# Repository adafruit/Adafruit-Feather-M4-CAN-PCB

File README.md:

## Adafruit Feather M4 CAN Express PCB

<a href="http://www.adafruit.com/products/4759"><br/>
Click here to purchase one from the Adafruit shop</a>

PCB files for the Adafruit Feather M4 CAN Express.

Format is EagleCAD schematic and board layout
* https://www.adafruit.com/product/4759

### Description

One of our favorite Feathers, the Feather M4 Express, gets a glow-up here with an upgrade to the SAME51 chipset which has built-in CAN bus support!  Like its SAMD51 cousin, the ATSAME51J19 comes with a 120MHz Cortex M4 with floating point support and 512KB Flash and 192KB RAM. Your code will zig and zag and zoom, and with a bunch of extra peripherals for support, this will for sure be your favorite new chipset for CAN interfacing projects.

At the end of the board we have placed a CAN transceiver chip as well as a 5V converter to generate 5V power to the transceiver even when running on battery. The two CAN signal lines and ground reference signal are available on a 3-pin 3.5mm terminal block. The chip and booster can be put to sleep for power saving. The built in CAN can read or write packets and has support in both Arduino and CircuitPython.

And best of all, it's a Feather - so you know it will work with all our FeatherWings! What a great way to quickly get up and running. It's even pin-compatible with the original Feather M4.

The most exciting part of the Feather M4 CAN is that while you can use it with the Arduino IDE - and it's bonkers fast when you do, you can use it with CircuitPython as well. When you plug it in, it will show up as a very small disk drive with main.py on it. Edit main.py with your favorite text editor to build your project using Python, the most popular programming language. No installs, IDE or compiler needed, so you can use it on any computer, even ChromeBooks or computers you can't install software on. When you're done, unplug the Feather and your code will go with you.

Here are some of the updates you can look forward to when using Feather M4 CAN:

* Measures 2.0" x 0.9" x 0.28" (50.8mm x 22.8mm x 7mm) without headers soldered in
* Light as a (large?) feather - 5 grams
* ATSAME51 32-bit Cortex M4 core running at 120 MHz, 32-bit, 3.3V logic and power
* Hardware CAN bus support with built-in transceiver, 5V booster and terminal connection.
* Floating point support with Cortex M4 DSP instructions
* 512 KB flash, 192 KB RAM
* 2 MB SPI FLASH chip for storing files and CircuitPython code storage.
* No EEPROM
* 32.768 KHz crystal for clock generation & RTC
* 3.3V regulator with 500mA peak current output
* USB Type C connector for USB native support, comes with USB bootloader and serial port debugging
* Built in crypto engines with AES (256 bit), true RNG, Pubkey controller
* Tons of GPIO! 21 x GPIO pins with following capabilities:
  * Dual 1 MSPS 12 bit true analog DAC (A0 and A1) - can be used to play 12-bit stereo audio clips
  * Dual 1 MSPS 12 bit ADC (6 analog pins some on ADC1 and some on ADC2)
  * 6 x hardware SERCOM - Native hardware SPI, I2C and Serial all available
  * 16 x PWM outputs - for servos, LEDs, etc
  * I2S input and output
  * 8-bit Parallel capture controller (for camera/video in)
* Built in 100mA lipoly charger with charging status indicator LED
* Pin #13 red LED for general purpose blinking
* Power/enable pin
* 4 mounting holes
* Reset button

The Feather M4 Can Express also comes with a Mini NeoPixel and 2 MB SPI Flash storage. You can use the SPI Flash storage like a very tiny hard drive. When used in CircuitPython, the 2 MB flash acts as storage for all your scripts, libraries and files. When used in Arduino, you can read/write files to it, like a little datalogger or SD card, and then with our helper program, access the files over USB.

Easy reprogramming: the Feather M4 CAN comes pre-loaded with the UF2 bootloader, which looks like a USB storage key. Simply drag firmware on to program, no special tools or drivers needed! It can be used to load up CircuitPython or Arduino IDE (it is bossa-compatible)

Comes fully assembled and tested, with the UF2 USB bootloader. We also toss in some headers so you can solder it in and plug into a solderless breadboard.

Lipoly battery and USB cable not included (but we do have lots of options in the shop if you'd like!)

### License

Adafruit invests time and resources providing this open source design, please support Adafruit and open-source hardware by purchasing products from [Adafruit](https://www.adafruit.com)!

Designed by Limor Fried/Ladyada for Adafruit Industries.

Creative Commons Attribution/Share-Alike, all text above must be included in any redistribution.
See license.txt for additional details.

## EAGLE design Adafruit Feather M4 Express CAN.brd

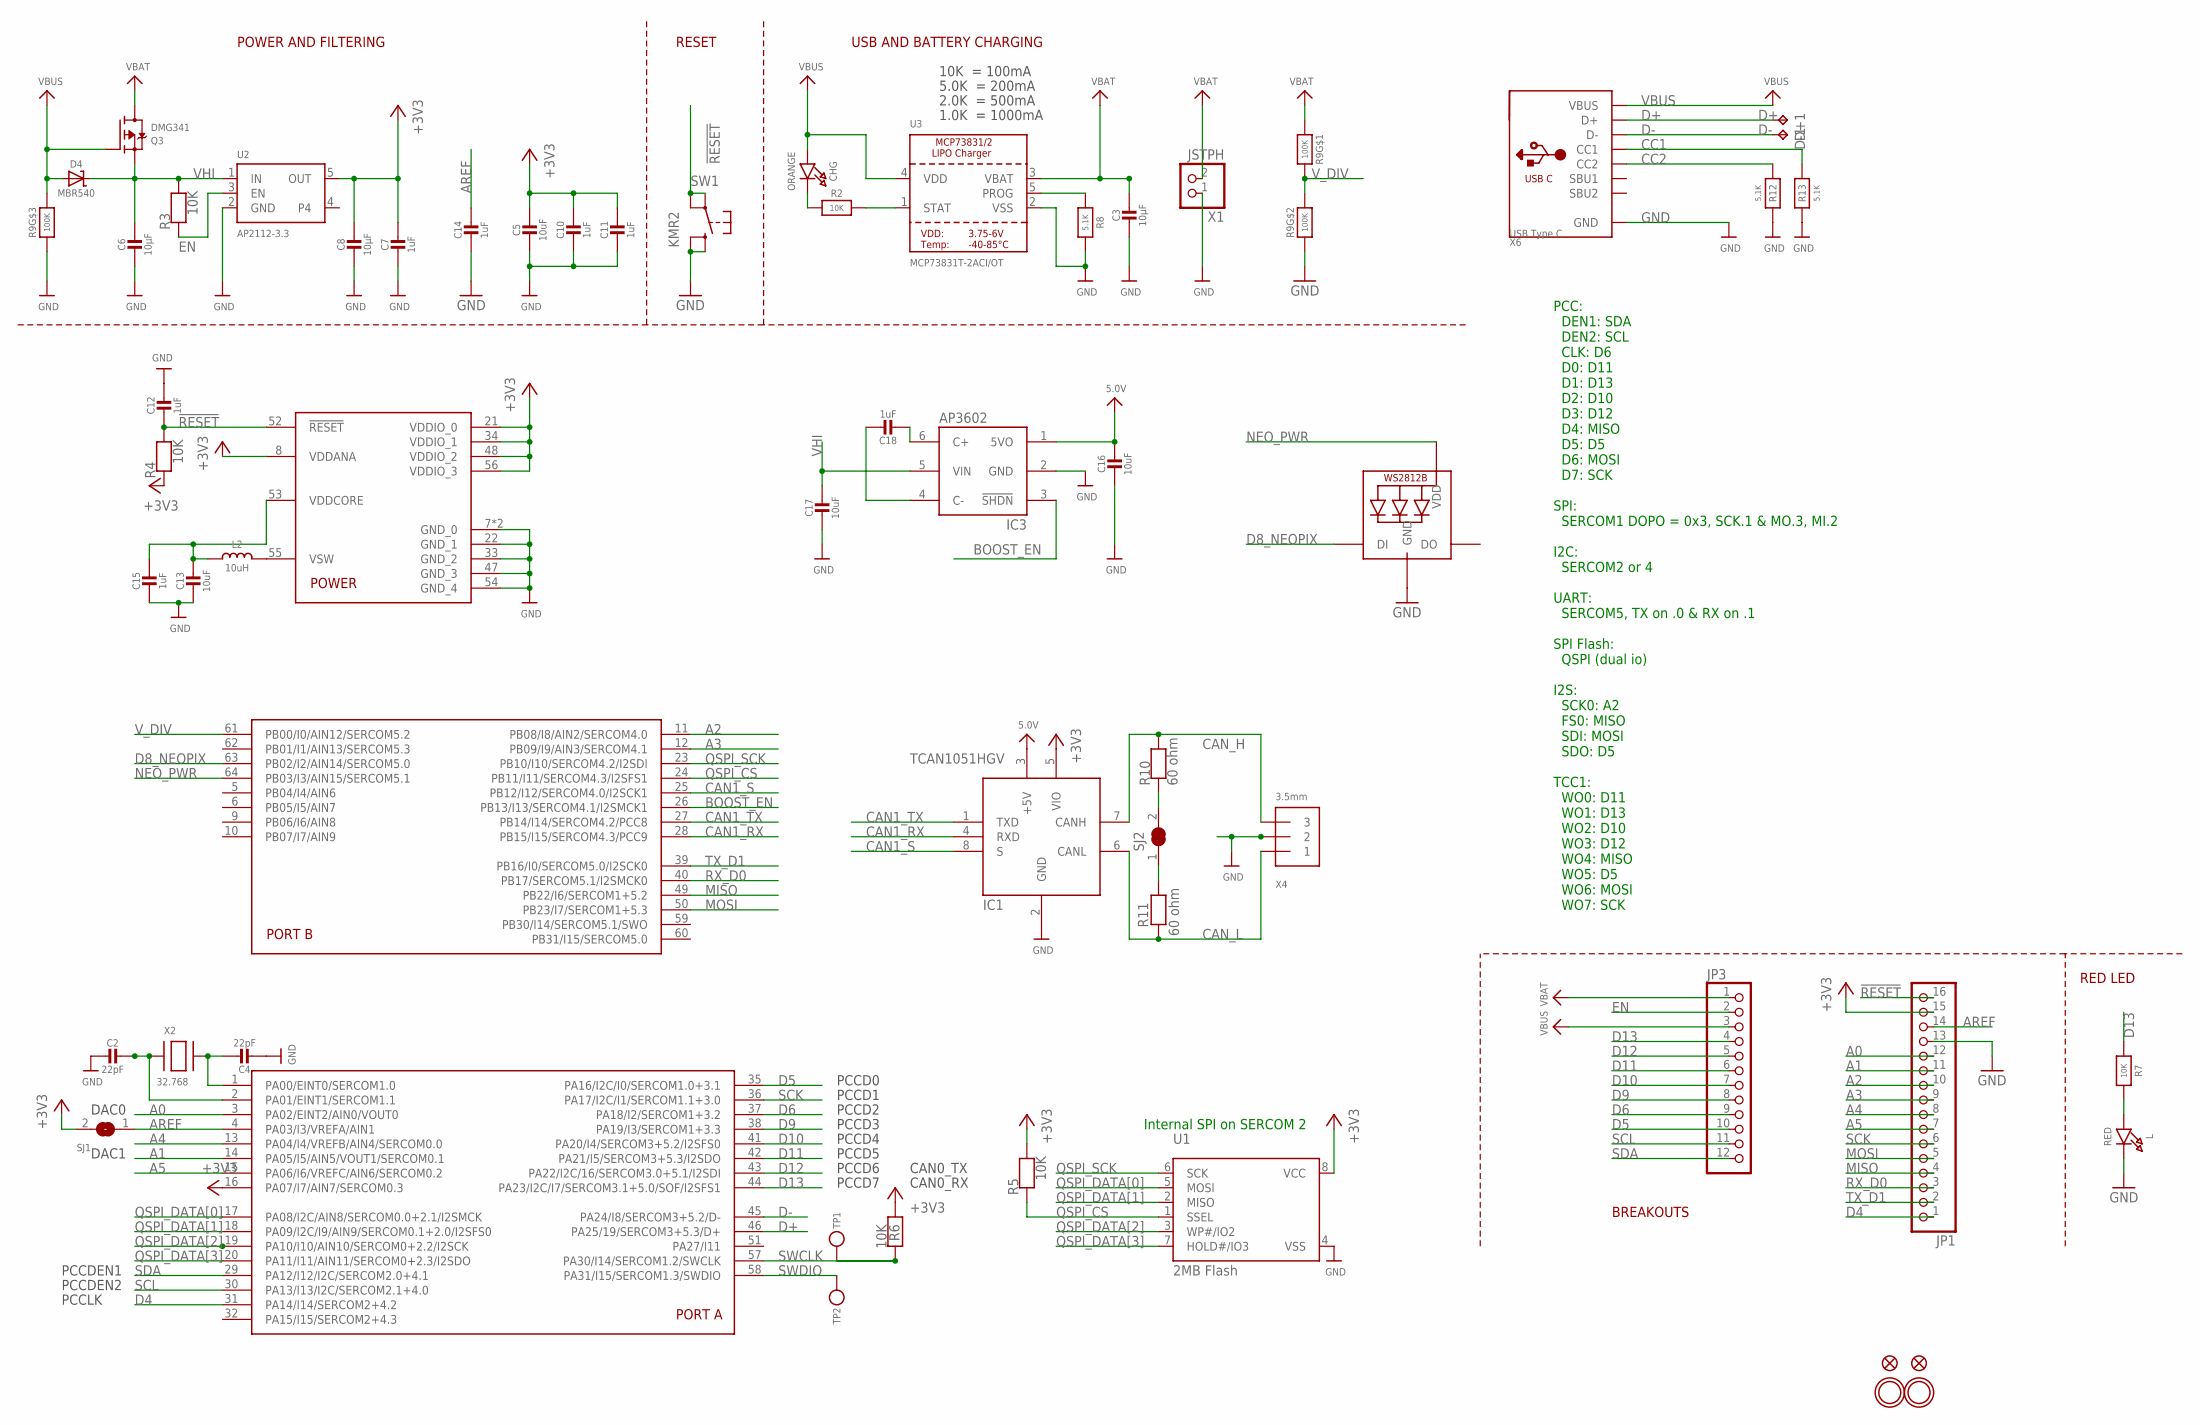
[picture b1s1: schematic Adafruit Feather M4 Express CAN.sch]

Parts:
C2, C4: 22pF; 0603-NO
C3, C6, C8: 10µF; 0805-NO
C5, C13, C17: 10uF; 0805-NO
C7, C10, C11, C12, C14, C15: 1uF; 0603-NO
C16: 10uF; _0805MP
C18: 1uF; 0805_10MGAP
CHG: ORANGE; CHIPLED_0603_NOOUTLINE
D4: MBR540; SOD-123
D+1: TPB1,27; B1,27
D-1: TPB1,27; B1,27
IC1: TCAN1051HGV; SOIC8_150MIL
IC3: AP3602; SOT23-6
JP1: HEADER-1X16ROUND; 1X16_ROUND
JP3: HEADER-1X12; 1X12_ROUND
L: RED; CHIPLED_0603_NOOUTLINE
L2: 10uH; INDUCTOR_1007
LED1: WS2812B3535; LED3535
Q3: DMG341; SOT23-R
R2, R3, R4, R5, R6, R7: 10K; 0603-NO
R8, R12, R13: 5.1K; 0603-NO
R9: 100K; RESPACK_4X0603_NO
R10, R11: 60 ohm; 0805-NO
SJ1: SOLDERJUMPERCLOSED; SOLDERJUMPER_CLOSEDWIRE
SJ2: SOLDERJUMPER_CLOSED; SOLDERJUMPER_CLOSEDWIRE
SW1: KMR2; BTN_KMR2_4.6X2.8
TP1, TP2: TESTPOINTROUND1.5MM; TESTPOINT_ROUND_1.5MM
U1: 2MB Flash; USON8
U2: AP2112-3.3; SOT23-5@1
U3: MCP73831T-2ACI/OT; SOT23-5
U$14: ATSAMD51J; PQFN64-1
U$31, U$32: MOUNTINGHOLE2.5; MOUNTINGHOLE_2.5_PLATED
U$34, U$35: FIDUCIAL_1MM
X1: JSTPH; JSTPH2_BATT
X2: 32.768; XTAL3215
X4: 3.5mm; TERMBLOCK_1X3-3.5MM
X6: USB Type C; USB_C_CUSB31-CFM2AX-01-X

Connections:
5.0V: C16.1, IC1.3 (+5V), IC3.1 (5VO)
!RESET: C12.2, JP1.16, R4.2, SW1.A, SW1.A' (P1), U$14.52 (!RESET)
+3V3: C5.1, C7.1, C8.1, C10.1, C11.1, IC1.5 (VIO), JP1.15, R4.1, R5.2, R6.1, SJ1.2, U1.8 (VCC), U2.5 (OUT), U$14.8 (VDDANA), U$14.16 (PA07/I7/AIN7/SERCOM0.3), U$14.21 (VDDIO_0), U$14.34 (VDDIO_1), U$14.48 (VDDIO_2), U$14.56 (VDDIO_3)
A0: JP1.12, U$14.3 (PA02/EINT2/AIN0/VOUT0)
A1: JP1.11, U$14.14 (PA05/I5/AIN5/VOUT1/SERCOM0.1)
A2: JP1.10, U$14.11 (PB08/I8/AIN2/SERCOM4.0)
A3: JP1.9, U$14.12 (PB09/I9/AIN3/SERCOM4.1)
A4: JP1.8, U$14.13 (PA04/I4/VREFB/AIN4/SERCOM0.0)
A5: JP1.7, U$14.15 (PA06/I6/VREFC/AIN6/SERCOM0.2)
AREF: C14.1, JP1.14, SJ1.1, U$14.4 (PA03/I3/VREFA/AIN1)
BOOST_EN: IC3.3 (!SHDN), U$14.26 (PB13/I13/SERCOM4.1/I2SMCK1)
CAN1_RX: IC1.4 (RXD), U$14.28 (PB15/I15/SERCOM4.3/PCC9)
CAN1_S: IC1.8 (S), U$14.25 (PB12/I12/SERCOM4.0/I2SCK1)
CAN1_TX: IC1.1 (TXD), U$14.27 (PB14/I14/SERCOM4.2/PCC8)
CAN_H: IC1.7 (CANH), R10.2, X4.3
CAN_L: IC1.6 (CANL), R11.2, X4.1
CC1: R13.2, X6.A5 (CC1)
CC2: R12.2, X6.B5 (CC2)
D4: JP1.1, U$14.31 (PA14/I14/SERCOM2+4.2)
D5: JP3.10, U$14.35 (PA16/I2C/I0/SERCOM1.0+3.1)
D6: JP3.9, U$14.37 (PA18/I2/SERCOM1+3.2)
D8_NEOPIX: LED1.1 (DI), U$14.63 (PB02/I2/AIN14/SERCOM5.0)
D9: JP3.8, U$14.38 (PA19/I3/SERCOM1+3.3)
D10: JP3.7, U$14.41 (PA20/I4/SERCOM3+5.2/I2SFS0)
D11: JP3.6, U$14.42 (PA21/I5/SERCOM3+5.3/I2SDO)
D12: JP3.5, U$14.43 (PA22/I2C/16/SERCOM3.0+5.1/I2SDI)
D13: JP3.4, R7.1, U$14.44 (PA23/I2C/I7/SERCOM3.1+5.0/SOF/I2SFS1)
D+: D+1.TP, U$14.46 (PA25/19/SERCOM3+5.3/D+), X6.A6 (D+), X6.B6 (D+)
D-: D-1.TP, U$14.45 (PA24/I8/SERCOM3+5.2/D-), X6.A7 (D-), X6.B7 (D-)
EN: JP3.2, R3.1, U2.3 (EN)
GND: C2.2, C3.2, C4.2, C5.2, C6.2, C7.2, C8.2, C10.2, C11.2, C12.1, C13.2, C14.2, C15.2, C16.2, C17.2, IC1.2 (GND), IC3.2 (GND), JP1.13, L.C, LED1.4 (GND), R8.2, R9.3 (1), R9.7 (2), R12.1, R13.1, SW1.B (S), SW1.B' (S1), U1.4 (VSS), U2.2 (GND), U3.2 (VSS), U$14.7 (GND_0), U$14.22 (GND_1), U$14.33 (GND_2), U$14.47 (GND_3), U$14.54 (GND_4), U$14.EXP (GND_0), X1.1, X4.2, X6.A1B12 (GND), X6.B1A12 (GND)
MISO: JP1.4, U$14.49 (PB22/I6/SERCOM1+5.2)
MOSI: JP1.5, U$14.50 (PB23/I7/SERCOM1+5.3)
unnamed: CHG.C, R2.1
unnamed: L.A, R7.2
unnamed: R2.2, U3.1 (STAT)
unnamed: R8.1, U3.5 (PROG)
unnamed: R10.1, SJ2.2
unnamed: C4.1, U$14.1 (PA00/EINT0/SERCOM1.0), X2.P$2
unnamed: C18.2, IC3.6 (C+)
unnamed: C18.1, IC3.4 (C-)
unnamed: C2.1, U$14.2 (PA01/EINT1/SERCOM1.1), X2.P$1
unnamed: L2.P$2 (2), U$14.55 (VSW)
unnamed: R11.1, SJ2.1
NEO_PWR: LED1.2 (VDD), U$14.64 (PB03/I3/AIN15/SERCOM5.1)
QSPI_CS: R5.1, U1.1 (SSEL), U$14.24 (PB11/I11/SERCOM4.3/I2SFS1)
QSPI_DATA[0]: U1.5 (MOSI), U$14.17 (PA08/I2C/AIN8/SERCOM0.0+2.1/I2SMCK)
QSPI_DATA[1]: U1.2 (MISO), U$14.18 (PA09/I2C/I9/AIN9/SERCOM0.1+2.0/I2SFS0)
QSPI_DATA[2]: U1.3 (WP#/IO2), U$14.19 (PA10/I10/AIN10/SERCOM0+2.2/I2SCK)
QSPI_DATA[3]: U1.7 (HOLD#/IO3), U$14.20 (PA11/I11/AIN11/SERCOM0+2.3/I2SDO)
QSPI_SCK: U1.6 (SCK), U$14.23 (PB10/I10/SERCOM4.2/I2SDI)
RX_D0: JP1.3, U$14.40 (PB17/SERCOM5.1/I2SMCK0)
SCK: JP1.6, U$14.36 (PA17/I2C/I1/SERCOM1.1+3.0)
SCL: JP3.11, U$14.30 (PA13/I13/I2C/SERCOM2.1+4.0)
SDA: JP3.12, U$14.29 (PA12/I12/I2C/SERCOM2.0+4.1)
SWCLK: R6.2, TP1.P$1, U$14.57 (PA30/I14/SERCOM1.2/SWCLK)
SWDIO: TP2.P$1, U$14.58 (PA31/I15/SERCOM1.3/SWDIO)
TX_D1: JP1.2, U$14.39 (PB16/I0/SERCOM5.0/I2SCK0)
VBAT: C3.1, JP3.1, Q3.3 (D), R9.8 (2), U3.3 (VBAT), X1.2
VBUS: CHG.A, D4.A, JP3.3, Q3.1 (G), R9.6 (2), U3.4 (VDD), X6.A4B9 (VBUS), X6.B4A9 (VBUS)
VDDCORE1: C13.1, C15.1, L2.P$1 (1), U$14.53 (VDDCORE)
VHI: C6.1, C17.1, D4.C, IC3.5 (VIN), Q3.2 (S), R3.2, U2.1 (IN)
V_DIV: R9.1, R9.2 (1), U$14.61 (PB00/I0/AIN12/SERCOM5.2)

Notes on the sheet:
POWER AND FILTERING
RESET
10K = 100mA
5.0K = 200mA
2.0K = 500mA
1.0K = 1000mA
USB AND BATTERY CHARGING
BREAKOUTS
RED LED
Internal SPI on SERCOM 2
PCCDEN1
PCCDEN2
PCCD0
PCCD1
PCCD2
PCCD3
PCCD4
PCCD5
PCCD6
PCCD7
PCCLK
PCC: DEN1: SDA DEN2: SCL CLK: D6 D0: D11 D1: D13 D2: D10 D3: D12 D4: MISO D5: D5 D6: MOSI D7: SCK SPI: SERCOM1 DOPO = 0x3, SCK.1 & MO.3, MI.2 I2C: SERCOM2 or 4 UART: SERCOM5, TX on .0 & RX on .1 SPI Flash: QSPI (dual io) I2S: SCK0: A2 FS0: MISO SDI: MOSI SDO: D5 TCC1: WO0: D11 WO1: D13 WO2: D10 WO3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
CAN0_TX
CAN0_RX
DAC0
DAC1

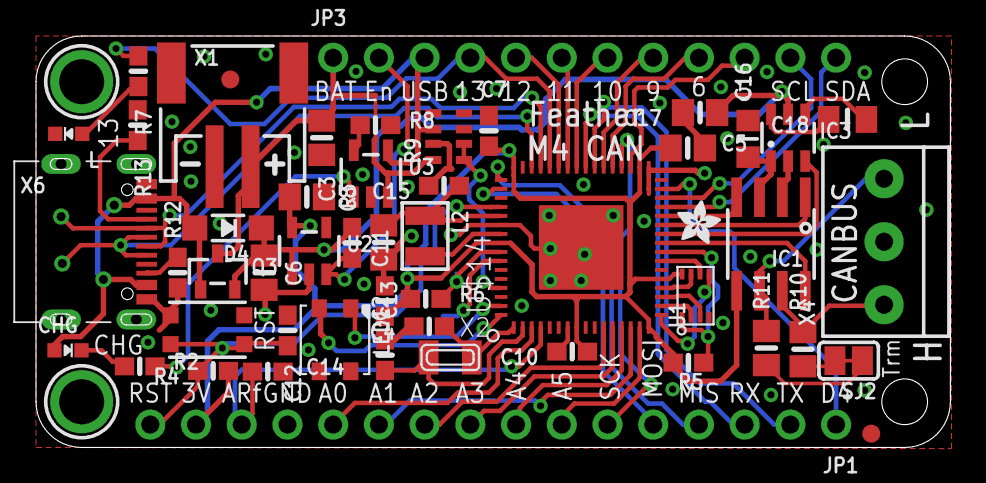
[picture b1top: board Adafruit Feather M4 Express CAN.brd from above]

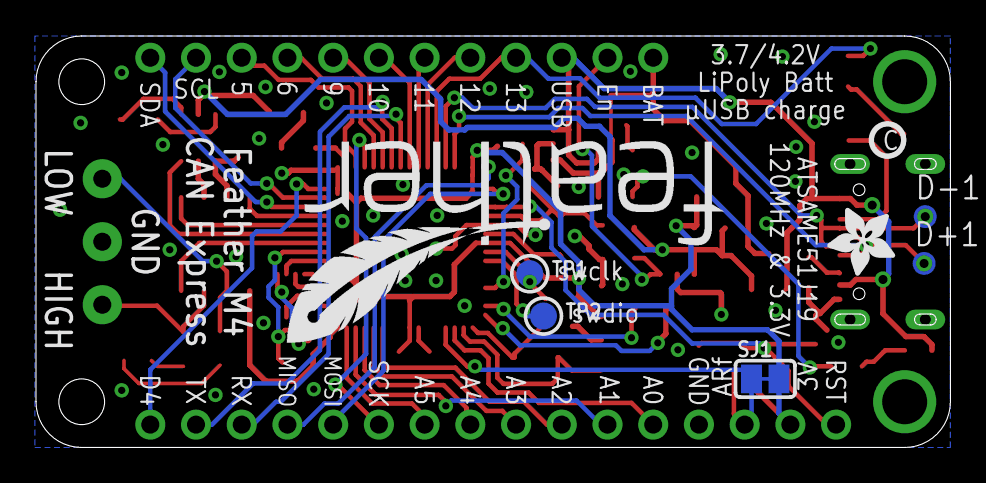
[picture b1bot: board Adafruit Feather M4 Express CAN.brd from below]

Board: 2 copper layers, 50.8 x 22.9 mm, 61 parts (8 on the bottom side), 63 nets.

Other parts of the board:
U$1: ADAFRUIT_2.5MM
U$9: FEATHERLOGO
U$12: ADAFRUIT_3.5MM
U$13: PCBFEAT-REV-040

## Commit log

2020-12-08 Adding board files.
2022-05-02 Added PrettyPins

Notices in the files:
parts and their libraries:
microbuilder: This work is placed in the public domain, and may be freely used for commercial and non-commercial work with the following conditions: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
